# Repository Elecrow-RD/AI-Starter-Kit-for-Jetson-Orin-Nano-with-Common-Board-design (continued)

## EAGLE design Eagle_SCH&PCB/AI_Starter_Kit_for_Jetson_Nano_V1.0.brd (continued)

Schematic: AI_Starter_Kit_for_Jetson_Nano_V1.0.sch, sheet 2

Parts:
BUZ1: BUZZER_1295; BUZZER_0955_DIP
C15, C33, C52, C53, C66, C67, C68, C69, C70, C72, C73, C76, C226: 1uF; C0603
C16, C18, C19, C20, C21, C22, C23, C24, C25, C26, C27, C28, C29, C30, C31, C32, C34, C35, C36, C37, C40, C49, C50, C54, C55, C58, C64, C74, C88, C95, C100, C112, C138, C144, C145, C146, C148, C149, C177, C209, C220: 100nF; C0603
C38, C39: 1nF; C0603
C41, C221, C227, C228: 10nF; C0603
C42: 22uF; C0805
C44, C45, C56, C71, C75, C77, C78, C79, C135, C147, C166, C213, C214: 4.7uF; C0603
C51, C80, C81: 220nF; C0603
C86, C136, C139: 2.2uF; C0603
C101, C102: 33pF; C0603
C105, C106: 330pF; C0603
C107, C109, C111, C179: 15pF; C0603
C129, C222, C224: 22nF; C0603
C133, C134, C212: 12pF; C0603
C176, C178, C223: 10uF; C0805
C225: 47uF; C0805
D001, D003: 1N4148; D_SOD123
D11: RED; LED-8MM
EC1: Encoder; 5P-13.75X11.7X6.5H
FB6, FB10: 10uH; L0603
FB9: FB 220R/MH2012HM221-T; L0805
J1, J4: H_22_2.54; P4_2.54*4_VIA
J2: Gas Sensor Socket; MQ2
J3: ST150(ZD); 2*2P-IR928
J5, J6, J21, J22: PH2.0-4P; 4P-SMD-2.0
J9: SERVO_1; 1X03
J10: SERVO_2; 1X03
J12: IR-3PSIP3; VS1838B-SIP3
J14: RGB6464AMD; RGB64*64AMD
J23: SERVO; 4P-SMD-2.0
J123: 3.5MM3P; 3.5MM*3P
J138: CROWPI_POW_SMD-2.54MM5P; CROWPI_POW_SMD-5P*2.54
J233: Ultrasonic; ULTRA
J313: MOTOR_1CN; MOTOR_1CM
K1, K2, K3, K4: BUTTON_2P
K5: ROCKER
K6, K7: BUTTON; 157SW
K10: RELAY-SRD; REY5-6-19.1X15.5X15.3MM
K11: TILT-DIP-2P; TILT
L14: CD32_950MA; CD32
L103, L104: 2.2uH; 0805@1
LED1, LED6: RED; DISCRETE_LED-0603
P1, P2, P3, P4, P5, P6, P10, P13, P17, P25, P26, P27, P28, P29, P30, P31, P32, P33, P34, P35, P36, P37, P38, P39, P40, P41, P42, P43, P44, P45, P46, P47, P55, P56, P57, P59, P60, P61, P62, P63, P69, P70, P73, P74, P76, P77, P78, P79, P80, P81, P82, P83, P84, P109, P110, P111, P112, P113, P114, P115, P116: PADPAD-1.0MM; PAD-1.0MM
P66, P104: TEST_PAD; TEST_PAD-1.0MM
P75, P105, P106, P107, P108: IO_RGB; PAD-1.0MM
P101: KEY; 1P-D450
Q3, Q5, Q103, Q104, Q108, Q115: S9013; SOT23@1
Q6, Q9: AO3401A; PMOS_SOT23
Q7, Q8, Q106, Q107: BSS138; SOT23
R1, R100: 100K; R0603
R13: 5.1R; R0603
R14, R23, R29, R30, R31, R43, R45, R72, R73, R81, R84, R85, R101, R108, R131, R132, R133, R134, R239, R240, R248, R257, R259: 4.7K; R0603
R15: MF52A103F3950; RES-TH_L2.5-W2.5-P1.70-D0.3
R16, R17, R21, R26, R27, R28, R36, R42, R63, R64, R65, R77, R87, R89, R94, R104, R109, R113, R127, R231, R237, R242, R249, R251, R253, R255, R273, R280, R286, R288, R302, R308, R324, R325: 10K; R0603
R18, R19, R102, R105, R106, R111, R189, R238, R256, R258, R260: NC; R0603
R22: 270R; R0603
R24, R32, R33, R35, R107, R140, R246, R282, R287, R321, R364, R639: 1K; R0603
R25, R71: 470R; R0603
R34, R39, R82, R83, R128, R129, R135, R136, R221, R243, R272, R298: 0R; R0603
R74, R254, R299: 2K; R0603
R75, R76: 47K; R0603
R79, R110: 4.7k; R0603
R112, R284: 100R; R0603
R115, R116, R125, R130, R276, R283, R292, R293, R294, R297, R303: 22R; R0603
R219: 30.9K; R0603
R244: 130K; R0603
R245: 500K; 3P-SMD-SQUA-3.6X3.3
R247, R250, R252: 1M; R0603
R268: 10K; 3P-SMD-SQUA-3.6X3.3
R328: 5.1K; R0603
R367: 820R; R0603
R652: 2.7K; R0603
R653: 3.74K; R0603
R654: 5.6K; R0603
R655: 8.2K; R0603
RP1: R-POTENTIOMETER; 3P-SQUA-45.6X10X5.8H
SW1: switch_6pin; SWITCH_6PIN_2P
U2: LSM6DS3TR-C; LGA-14L
U4: KTH1701FH-ST3; SOT-23W
U6, U7: RT9013-33GB-MS; SOT23-5
U8, U35: MMDT3906; SOT-363
U9: DHT20; CROWTAIL-DHT20-V1.0-20211013_DHT20
U13: SPL06-001; LGA8-0.65-2X2.5X0.95MM
U16: TCA9534APWR; SOP65P640X120-16N
U18: KT0210-QFN40-EP; QFN40_EP
U19: WMM7027ATSN1-4/TR; LGA-4(1.9X2.8)
U24: SN74LVC1G125; SOT23-5
U25: MT2492; MT2492-SOT23-6
U27: RP2040_RP2040; RP2040_QFN-56
U29: SELF_W25Q128JV; SELF_SOIC-8-208MIL
U31: STC8H1K28-36I-LQFP32; QFP80P900X900X165-32N
U39: PCF8574DWR(UMW); SO-16-300MIL
U103: LPW5206AB5F; IC_SOT23-5
U114: ULN2003D
U115: MFRC522; RC522
U121: BH1750; B1750
U123: TTP223; SOT23-6L
U125: LM358; SOP8@1
U126: BISS0001DRG; SOP16
U131: D203S; PIR_MOTION_SENSOR_3P-D8.1MM
U205: HT16K33-20P; HT16K33-SOP20
U215: YY2841AS-33; 4-DIGITAL_DISPLAY
U235: LCD1602; LCD1206
U$66, U$69, U$70, U$71, U$164, U$165: PADPAD1; PAD_5*3
X2: 12MHZ_SMD3225; A_XBJ_SMD3225
X102: 27.12MHZ; CRYSTAL-3.2-2.5

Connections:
3V3_IO: J5.3, J6.3, J23.3, P41.P$1, P83.P$1, Q9.2 (S), U8.4 (E2)
5V_IO: J21.3, J22.3, P79.P$1, Q6.2 (S), U35.4 (E2)
5V_SERVO_1: J10.3, P35.P$1, Q8.3 (D), R134.2
5V_SERVO_2: J9.3, P33.P$1, Q7.3 (D), R133.2
+1V1: C23.1, C64.1, C86.1, U27.23 (VDD_1V1), U27.45 (LDO_OUT), U27.50 (VDD_1V1)
+5V_SYS: C16.2, C19.2, C30.2, C31.2, C32.1, C35.2, C40.1, C42.1, C45.1, C54.1, C56.1, C67.1, C69.1, C74.2, C176.1, FB9.2, J4.1, J4.1-1, J9.2, J10.2, J138.P$1 (1), P36.P$1, P42.P$1, Q6.3 (D), R17.1, R25.1, R29.1, R72.1, R73.1, R74.1, R87.1, R89.1, R127.1, R133.1, R134.1, R257.1, R259.1, R268.3 (2), R283.1, R303.1, R324.1, SW1.2 (2_COM2), U6.1, U6.3, U7.1, U7.3, U16.16 (VCC), U18.7 (VDD5V), U18.24 (VDD5V_DRI), U25.5 (IN), U35.1 (E1), U39.P$16 (VDD), U114.9 (COM), U205.P$20, U235.P$2 (2_VDD), U235.P$15 (15_LEDA); also elsewhere on the board
+5V_SYS_GAS: C25.2, J2.1 (A), J2.2 (H), J2.3 (A), R101.2, SW1.3 (3_2A)
A: U205.P$17, U215.11 (11_A)
ADC_CH0: K5.P$2 (COM1), P62.P$1, U31.1 (ADC0/P1.0)
ADC_CH1: K5.P$5 (COM2), P63.P$1, U31.2 (ADC1/P1.1)
ADC_CH2: C21.2, P113.P$1, RP1.2 (3), U31.3 (ADC2/P1.2)
ADC_CH3: J2.4 (B), J2.6 (B), P116.P$1, R14.1, U31.4 (ADC3/P1.3)
ADC_CH4: P61.P$1, R639.2, R652.2, R653.2, R654.2, R655.2, U31.5 (ADC4/P1.4)
ADC_CH5: C26.2, P70.P$1, R15.1, R16.2, U31.6 (ADC5/P1.5)
ANT1: R128.2, R129.2
AVDD: C136.1, R34.1, U27.43 (ADC_VDD)
AVDD3V: C53.1, C76.2, U18.6 (VDD2P8V), U18.27 (VDD2P8V_CG)
B: U205.P$16, U215.7 (7_B)
BOOT: K6.2, P10.P$1, P69.P$1, R35.2
BUZZER: P114.P$1, R284.1, U31.31 (ADC10/P0.2)
C: U205.P$15, U215.4 (4_C)
COM: J123.2, K10.2
CSB: U13.2 (CSB)
D: U205.P$14, U215.2 (2_D)
D2/I2C1_SDA: Q107.2 (S), R18.1, R39.2, R240.2, R260.1, U2.14 (SDA), U9.2 (SDA), U13.3 (SDA), U31.25 (I2CSDA_2/P2.4), U121.4 (SDA); also elsewhere on the board
D3/I2C1_SCL: Q106.2 (S), R19.1, R239.2, R258.1, R272.2, U2.13 (SCL), U9.4 (SCL), U13.4 (SCL), U31.26 (I2CSCL_2/P2.5), U121.6 (SCL); also elsewhere on the board
D4: P84.P$1, R298.2, R364.2; also elsewhere on the board
D6: C33.1, P13.P$1, R63.1, U4.2 (VOUT); also elsewhere on the board
D8/SPI0_CS0: U115.24 (SDA/NSS/RX); also elsewhere on the board
D9/SPI0_MISO: U115.31 (D7/MISO/SCL/TX); also elsewhere on the board
D10/SPI0_MOSI: U115.30 (D6/ADR_0/MOSI); also elsewhere on the board
D11/SPI0_SCK: U115.29 (D5/ADR_1/SCK/DTRQ); also elsewhere on the board
D12/PWM: J6.1, P81.P$1; also elsewhere on the board
D13/PWM: J5.1, P82.P$1; also elsewhere on the board
D14/UART1_TXD: R125.1; also elsewhere on the board
D15/UART1_RXD: R130.1; also elsewhere on the board
D16/UART1_CTS: J233.P$3 (3_TRIG), P111.P$1; also elsewhere on the board
D17/UART1_RTS: P55.P$1, R287.2; also elsewhere on the board
D18/I2S0_SCLK: P27.P$1, R24.2; also elsewhere on the board
D20/I2S0_SDIN: J12.3, P112.P$1, R140.1; also elsewhere on the board
D23/SPI1_CS1: P57.P$1, R189.1, R254.2; also elsewhere on the board
D25/SPI1_MISO: P109.P$1, U125.1 (1_OUT1), U125.2 (2_IN1-); also elsewhere on the board
D26/SPI1_MOSI: P110.P$1, R299.2; also elsewhere on the board
D27/SPI1_SCK: P2.P$1, R282.1; also elsewhere on the board
DB4: U39.P$9 (P4), U235.P$11 (11_D4)
DB5: U39.P$10 (P5), U235.P$12 (12_D5)
DB6: U39.P$11 (P6), U235.P$13 (13_D6)
DB7: U39.P$12 (P7), U235.P$14 (14_D7)
DIG1: U205.P$2, U215.12 (12_COM1)
DIG2: U205.P$3, U215.9 (9_COM2)
DIG3: U205.P$4, U215.8 (8_COM3)
DIG4: U205.P$5, U215.6 (6_COM4)
DIS_RGB: P74.P$1, U27.41 (GPIO29/ADC3)
DP: U205.P$10, U215.3 (3_DP)
E: U205.P$13, U215.1 (1_E)
ENCODER_A: C38.1, P59.P$1, R64.1, U16.11 (P6)
ENCODER_B: C39.2, P60.P$1, R65.1, U16.12 (P7)
ENCODER_SW: C66.2, R71.1, R74.2, U16.10 (P5)
E_LCD: U39.P$6 (P2), U235.P$6 (6_E)
F: U205.P$12, U215.10 (10_F)
G: U205.P$11, U215.5 (5_G)
GND: C15.1, C16.1, C18.1, C19.1, C20.2, C21.1, C22.2, C23.2, C24.2, C25.1, C26.1, C27.1, C28.1, C29.1, C30.1, C31.1, C32.2, C33.2, C34.1, C35.1, C36.1, C37.2, C38.2, C39.1, C40.2, C41.1, C42.2, C44.2, C45.2, C49.1, C53.2, C54.2, C55.1, C56.2, C58.1, C64.2, C66.1, C67.2, C68.2, C69.2, C70.2, C71.2, C72.2, C73.1, C74.1, C75.1, C76.1, C77.1, C78.1, C86.2, C88.2, C95.2, C101.2, C102.1, C105.1, C106.2, C111.1, C112.1, C133.2, C134.1, C135.2, C136.2, C138.2, C139.2, C144.2, C145.2, C146.2, C147.2, C148.2, C149.2, C166.2, C176.2, C177.1, C178.1, C179.1, C209.1, C212.1, C213.1, C214.1, C220.1, C221.1, C225.1, C226.2, C227.2, C228.2, EC1.2 (C), EC1.4 (GND), J1.3, J1.3-1, J3.1 (-), J3.3 (E), J4.3, J4.3-1, J5.4, J5.SS1, J5.SS2, J6.4, J6.SS1, J6.SS2, J9.1, J10.1, J12.2, J14.2, J14.4, J14.5, J14.6, J21.4, J21.SS1, J21.SS2, J22.4, J22.SS1, J22.SS2, J23.4, J23.SS1, J23.SS2, J138.P$6 (6), J138.P$7 (7), J233.P$1 (1_GND), K1.P$1, K2.P$1, K3.P$1, K4.P$1, K6.1, K7.1, K11.1, LED6.-, P17.P$1, P32.P$1, P37.P$1, P38.P$1, P43.P$1, P73.P$1, P80.P$1, Q3.2 (E), Q5.2 (E), Q103.2 (E), Q104.2 (E), Q108.2 (E), Q115.2 (E), R1.2, R13.1, R14.2, R15.2, R21.1, R23.2, R30.1, R31.1, R42.1, R75.2, R76.2, R77.2, R82.1, R83.1, R94.2, R100.2, R105.2, R108.1, R109.1, R111.1, R189.2, R238.1, R242.1, R250.2, R256.1, R268.1, R273.1, R280.1, R286.2, R288.2, R302.1, RP1.1, U2.6 (GND), U2.7 (GND), U4.3 (GND), U6.2, U7.2, U9.3 (GND), U13.1 (GND), U13.7 (GND), U16.1 (A0), U16.2 (A1), U16.8 (GND), U18.16 (DVSS), U18.34 (AUGND), U18.39 (DRVSS), U18.41 (GND), U19.2 (GND), U19.3 (GND), U24.1 (OE), U24.3 (GND), U25.2 (GND), U27.19 (TESTEN), U27.EPAD (GND), U29.4 (GND), U31.12 (GND/AGND), U39.P$8 (VSS), U103.2 (2_GND), U114.8 (GND), U115.1 (I2C), U115.4 (DVSS), U115.5 (PVSS), U115.10 (TVSS), U115.14 (TVSS2), U115.18 (AVSS), U115.33 (GND), U121.3 (GND\), U123.2 (GND), U125.4 (4_GND), U126.7 (VSS), U131.3 (G), U205.P$1, U235.P$1 (1_VSS), X2.2 (GND), X2.4 (GND), X102.2 (GND), X102.4 (GND); also elsewhere on the board
IN1: C212.2, P101.1, U123.3 (IN)
IN1+: R28.2, U125.3 (3_IN1+), U125.7 (7_OUT2)
INT1: P66.P$1, U2.4 (INT1)
INT2: P104.P$1, U2.9 (INT2)
IO_RGB: P75.P$1, U27.29 (GPIO18)
IO_RGB_POWER_EN: P76.P$1, U27.40 (GPIO28/ADC2)
ITR9606_IN: C41.2, J3.4 (C), P25.P$1, R27.2, U125.6 (6_IN2-)
JS_3V3: C15.2, C18.2, C24.1, C27.2, C28.2, C34.2, C37.1, C58.2, C70.1, C177.2, C178.2, C213.2, C214.2, C220.2, C226.1, J1.1, J1.1-1, J12.1, J233.P$4 (4VCC), Q7.1 (G), Q8.1 (G), Q9.3 (D), Q106.1 (G), Q107.1 (G), R16.1, R18.2, R19.2, R22.2, R26.1, R27.1, R28.1, R43.2, R45.1, R63.2, R84.1, R85.1, R113.2, R131.2, R132.2, R140.2, R237.2, R239.1, R240.1, R249.2, R251.2, R255.2, R308.1, R325.1, R364.1, R639.1, RP1.3 (2), U2.5 (VDDIO), U2.8 (VDD), U4.1 (VCC), U8.1 (E1), U9.1 (VCC), U13.6 (VDDIO), U13.8 (VDD), U31.10 (VCC/AVCC), U31.11 (ADC_VREF+), U115.2 (PVDD), U115.3 (DVDD), U115.12 (TVDD), U115.15 (AVDD), U121.1 (VCC), U123.5 (VCC), U125.8 (8_VCC), U126.11 (VDD), U131.1 (D); also elsewhere on the board
LIGHT: R321.2, U39.P$7 (P3)
MIC_3V3: C49.2, U7.5, U19.4 (VDD)
MIC_BIAS: C51.1, R79.1, R110.1, U18.3 (MIC_BIAS)
MIC_IN: C50.2, R110.2, U18.2 (KEY_IN)
MIC_USB_D+: R116.1; also elsewhere on the board
MIC_USB_D-: R115.1; also elsewhere on the board
unnamed: LED1.+, R81.1
unnamed: R1.1, U35.2 (B1), U35.5 (B2), U35.6 (C1)
unnamed: R17.2, U39.P$1 (A0)
unnamed: R87.2, U39.P$2 (A1)
unnamed: R89.2, U39.P$3 (A2)
unnamed: P6.P$1, U31.21 (P2.0)
unnamed: P5.P$1, U31.22 (P2.1)
unnamed: P4.P$1, U31.23 (P2.2)
unnamed: P3.P$1, U31.24 (P2.3)
unnamed: J1.2, J1.2-1, R135.1
unnamed: J1.4, J1.4-1, R136.1
unnamed: R42.2, R268.2 (3), U235.P$3 (3_V0)
unnamed: Q5.3 (C), U235.P$16 (16_LED_K)
unnamed: Q108.1 (B), R77.1, R321.1
unnamed: R82.2, U2.2 (SDX)
unnamed: J2.5 (H), R13.2
unnamed: C133.1, U27.20 (XIN), X2.1 (XIN)
unnamed: Q3.1 (B), R21.2, R24.1
unnamed: EC1.5 (SW), R71.2
unnamed: R244.1, R245.1
unnamed: R251.1, U126.8 (!RESET)
unnamed: J3.2 (+), R22.1
unnamed: R105.1, U103.3 (3_SET)
unnamed: R26.2, R94.1, U125.5 (5_IN2+)
unnamed: R221.2, U24.2 (IN_A)
unnamed: R29.2, U16.13 (INT)
unnamed: C209.2, R113.1, U121.5 (DVI)
unnamed: R127.2, U16.3 (A2)
unnamed: K5.P$1, R23.1
unnamed: C100.1, R328.1
unnamed: K5.P$6, R30.2
unnamed: K5.P$3, R43.1
unnamed: K5.P$4, R45.2
unnamed: R33.2, U27.21 (XOUT)
unnamed: P105.P$1, U27.2 (GPIO0)
unnamed: J313.P$2, Q104.3 (C)
unnamed: P106.P$1, U27.3 (GPIO1)
unnamed: P107.P$1, U27.4 (GPIO2)
unnamed: Q6.1 (G), R75.1, U35.3 (C2)
unnamed: R100.1, U8.2 (B1), U8.5 (B2), U8.6 (C1)
unnamed: R83.2, U2.3 (SCX)
unnamed: R84.2, U2.12 (CS)
unnamed: P108.P$1, U27.5 (GPIO3)
unnamed: D11.2 (C), Q3.3 (C)
unnamed: Q9.1 (G), R76.1, U8.3 (C2)
unnamed: K11.2, R298.1
unnamed: C129.1, L14.1, U25.6 (SW)
unnamed: LED6.+, R101.1
unnamed: D11.1 (A), R25.2
unnamed: R85.2, U2.1 (SDO)
unnamed: C50.1, R79.2, R102.1, U19.1 (OUT)
unnamed: C51.2, C52.2, U18.4 (DRVSS_SNS)
unnamed: R31.2, U13.5 (SDO)
unnamed: R108.2, R219.1, U25.3 (BF)
unnamed: Q108.3 (C), R32.2, R324.2
unnamed: C129.2, U25.1 (BS)
unnamed: R107.2, R109.2, U25.4 (EN)
unnamed: Q5.1 (B), R32.1
unnamed: C52.1, U18.5 (VREF_1P8V)
unnamed: FB10.2, U18.8 (DCDC1_SW)
unnamed: C71.1, FB10.1, U18.9 (DVDD1V)
unnamed: C72.1, U18.10 (DVDD3V)
unnamed: R111.2, U18.13 (GPIO6)
unnamed: R115.2, U18.22 (DM)
unnamed: R116.2, U18.21 (DP)
unnamed: C73.2, U18.23 (VDD3V_USB)
unnamed: FB6.1, U18.25 (DCDC2_SW)
unnamed: C75.2, FB6.2, U18.26 (VDD1P8V_CP)
unnamed: R104.1, U103.4 (4_EN)
unnamed: C77.2, U18.29 (CHP)
unnamed: C78.2, U18.28 (CHN)
unnamed: C79.1, U18.31 (CFLYP)
unnamed: C79.2, U18.30 (CFLYN)
unnamed: C134.2, R33.1, X2.3 (XOUT)
unnamed: C80.1, U18.35 (VINP)
unnamed: C81.1, U18.36 (VINN)
unnamed: P28.P$1, U18.12 (GPIO4)
unnamed: P29.P$1, U18.11 (GPIO3)
unnamed: K1.P$2, R652.1
unnamed: K2.P$2, R653.1
unnamed: K3.P$2, R654.1
unnamed: K4.P$2, R655.1
unnamed: R39.1, U27.31 (GPIO20)
unnamed: R272.1, U27.32 (GPIO21)
unnamed: R237.1, R238.2, U121.2 (ADDR)
unnamed: Q115.1 (B), R112.2, R273.2
unnamed: C29.2, J313.P$1, R283.2
unnamed: R288.1, U123.4 (AHLB), U123.6 (TOG)
unnamed: Q104.1 (B), R280.2, R282.2
unnamed: R286.1, R287.1, U123.1 (OUT)
unnamed: J138.P$2 (2), R297.2
unnamed: J138.P$3 (3), R292.2
unnamed: J138.P$4 (4), R293.2
unnamed: J138.P$5 (5), R294.2
unnamed: J233.P$2 (2_ECHO), R299.1
unnamed: Q103.1 (B), R284.2, R302.2
unnamed: BUZ1.2 (2-), D001.+, Q103.3 (C)
unnamed: BUZ1.1 (1+), C55.2, D001.-, R303.2
unnamed: R253.1, U126.3 (RR1)
unnamed: C228.1, R253.2, U126.4 (RC1)
unnamed: R254.1, U126.2 (VO)
unnamed: R252.1, U126.6 (RR2)
unnamed: C227.1, R252.2, U126.5 (RC2)
unnamed: C222.1, R245.2 (3), R245.3 (2), U126.12 (2OUT)
unnamed: C222.2, R244.2, R246.2, U126.13 (2IN-)
unnamed: R249.1, U126.9 (VC)
unnamed: R250.1, U126.10 (IB)
unnamed: C221.2, R242.2, R243.1, U131.2 (S)
unnamed: C223.2, C224.1, R247.1, U126.16 (1OUT)
unnamed: C224.2, R247.2, R248.2, U126.15 (1IN-)
unnamed: C223.1, R246.1
unnamed: C225.2, R248.1
unnamed: R255.1, R256.2, U126.1 (A)
unnamed: R243.2, U126.14 (1IN+)
unnamed: C111.2, U115.22 (OSCOUT), X102.1 (C1)
unnamed: C179.2, U115.21 (OSCIN), X102.3 (C2)
unnamed: C112.2, R367.1, U115.16 (VMID)
unnamed: C100.2, R367.2, U115.17 (RX)
unnamed: L104.1, U115.13 (TX2)
unnamed: L103.1, U115.11 (TX1)
unnamed: C101.1, C109.2, L103.2, R328.2
unnamed: C102.2, C107.2, L104.2
unnamed: R325.2, U115.6 (NRSTPD)
unnamed: R308.2, U115.32 (EA)
unnamed: C105.2, C109.1, R128.1
unnamed: C106.1, C107.1, R129.1
NC: J123.1, K10.4
NO: J123.3, K10.5
OUT1_S: P47.P$1, R297.1, U114.16 (OUT1)
OUT2_S: P46.P$1, R292.1, U114.15 (OUT2)
OUT3_S: P45.P$1, R293.1, U114.14 (OUT3)
OUT4_S: P44.P$1, R294.1, U114.13 (OUT4)
QSPI_CS: R35.1, R36.1, U27.56 (QSPI_!CS!), U29.1 (/CS)
QSPI_D0: U27.53 (QSPI_SD0), U29.5 (DI(IO0))
QSPI_D1: U27.55 (QSPI_SD1), U29.2 (DO(IO1))
QSPI_D2: U27.54 (QSPI_SD2), U29.3 (/WP(IO2))
QSPI_D3: U27.51 (QSPI_SD3), U29.7 (/HOLD/RESET(IO3))
QSPI_SCK: U27.52 (QSPI_SCLK), U29.6 (CLK)
RELAY: P115.P$1, R112.1, U31.30 (ADC9/P0.1)
RESET: C20.1, K7.2, P26.P$1, R231.1, U27.26 (RUN)
RGB_CTRO: J14.3, P56.P$1, U24.4 (Y)
RING2: C80.2, U18.37 (RING2_REF), U18.38 (RING2)
RP2040_3V3: C22.1, C68.1, C88.1, C138.1, C139.1, C144.1, C145.1, C146.1, C148.1, C149.1, R34.2, R36.2, R231.2, U6.5, U27.1 (VDDIO), U27.10 (VDDIO), U27.22 (VDDIO), U27.33 (VDDIO), U27.42 (VDDIO), U27.44 (LDO_IN), U27.48 (USB_VDD), U27.49 (VDDIO), U29.8 (VCC)
RP2040_IO6_RGB: P34.P$1, R221.1, U27.8 (GPIO6)
RP2040_IO13_SERVO_1: Q8.2 (S), R132.1, U27.16 (GPIO13)
RP2040_IO14_SERVO_2: Q7.2 (S), R131.1, U27.17 (GPIO14)
RP2040_IO27_RGB_POWER_EN: P31.P$1, R107.1, U27.39 (GPIO27/ADC1)
RS: U39.P$4 (P0), U235.P$4 (4_RS)
RW: U39.P$5 (P1), U235.P$5 (5_RW)
RX: J23.2, P40.P$1, R130.2
SA: EC1.1 (A), R64.2, R72.2
SB: EC1.3 (B), R65.2, R73.2
SCL: J21.1, J22.1, P78.P$1, Q106.3 (D), R257.2, R258.2, U16.14 (SCL), U39.P$14 (SCL), U205.P$18
SDA: J21.2, J22.2, P77.P$1, Q107.3 (D), R259.2, R260.2, U16.15 (SDA), U39.P$15 (SDA), U205.P$19
SLEEVE: C81.2, R102.2, U18.1 (SLE_REF), U18.40 (SLEEVE)
STC8_RXD: R135.2, U31.13 (P3.0/RXD)
STC8_TXD: R136.2, U31.14 (P3.1/TXD)
STEP1: U16.4 (P0), U114.1 (IN1)
STEP2: U16.5 (P1), U114.2 (IN2)
STEP3: U16.6 (P2), U114.3 (IN3)
STEP4: U16.7 (P3), U114.4 (IN4)
TX: J23.1, P39.P$1, R125.2
USB_D+: J4.4, J4.4-1, U27.47 (USB_D+)
USB_D-: J4.2, J4.2-1, U27.46 (USB_D-)
V+: K10.1, R276.2
V-: D003.+, K10.3, LED1.-, Q115.3 (C)
VCC_DIS_RGB: C135.1, C147.1, L14.2, P1.P$1, R104.2, R106.1, R219.2, U103.5 (5_VIN)
VCC_RELAY: C36.2, D003.-, FB9.1, R81.2, R276.1
VCC_RGB: C44.1, C95.1, C166.1, J14.1, P30.P$1, R106.2, U24.5 (VCC), U103.1 (1_OUT)

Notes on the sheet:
I2C
Temperature & Humidity(DHT20)
3V-5.5V
ADD:0X38
ADDRESS:0X38
ADDRESS:0111000
LIGHT SENSOR
ADD:0X5C
2.7V-4.2V
ADDRESS:0x5C
ADDRESS:1011100
Accelerometer&Gyro
Digital display
ADDRESS:0X70
ADDRESS:1110000
I2C_LCD
Custom_key
Joystick
Linear Potentiometer
NFC
GAS-MQ2
NTC
Barometer
ADDRESS:0X76
Ultrasonic Sensor
Buzzer
I2C-EXIO-STC8-P0.2
Relay
IR Remote Sensor
Vibration sensor
TTP223
Touch Sensor
D17
Tilt sensor
gold
sliver
Encoder
PIR-Motion sensor
D23
8*8RGB_LED

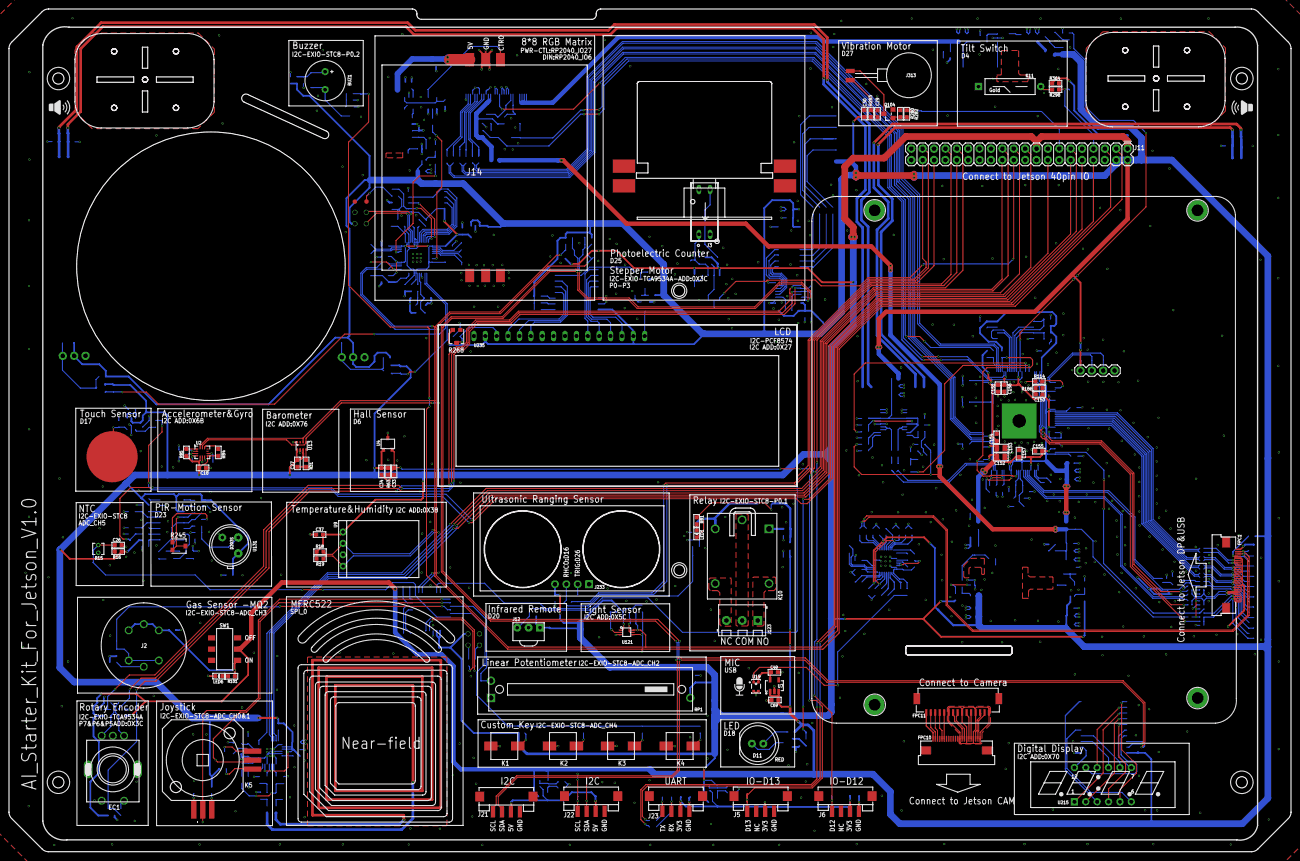
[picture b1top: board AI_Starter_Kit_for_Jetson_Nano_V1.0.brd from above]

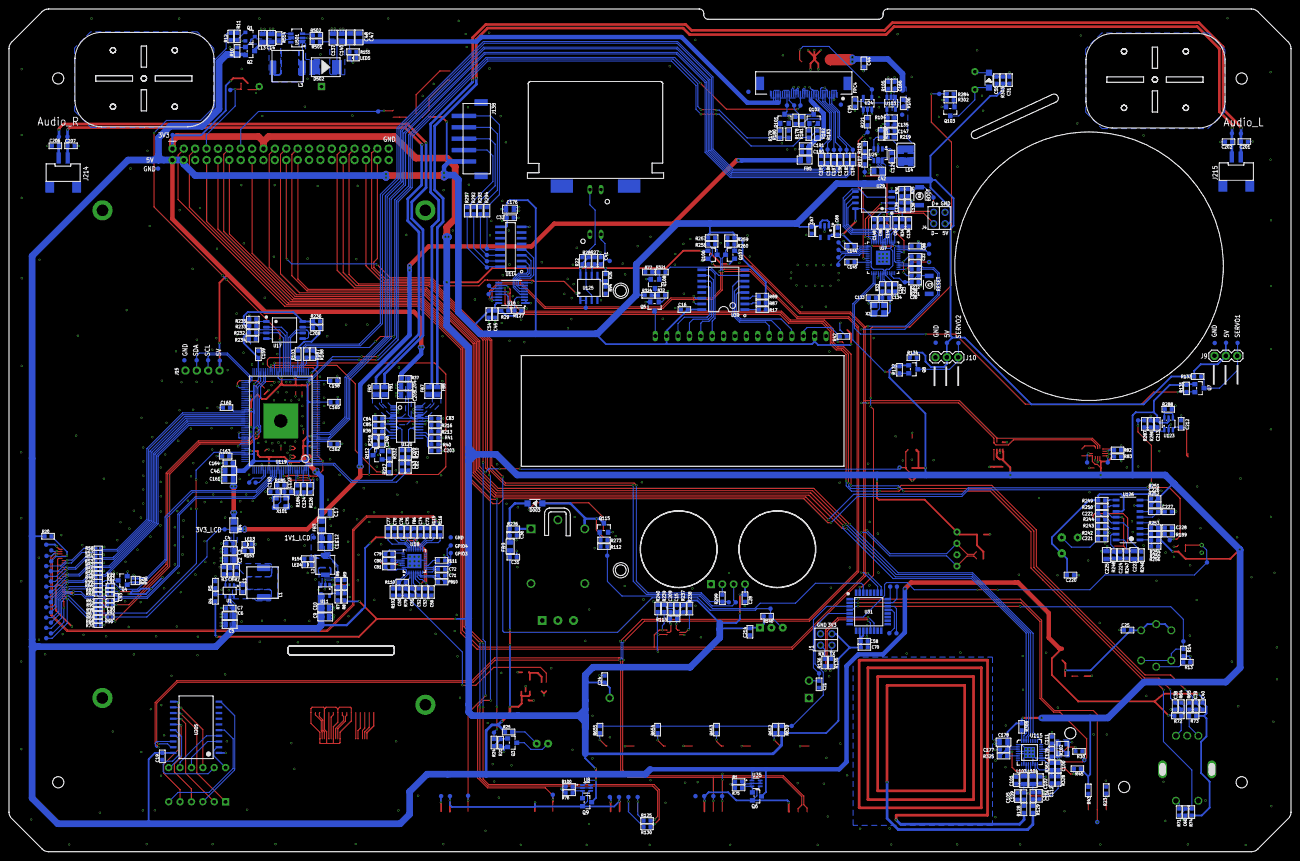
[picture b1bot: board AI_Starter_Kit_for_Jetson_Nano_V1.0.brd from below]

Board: 2 copper layers, 286.0 x 188.0 mm, 611 parts (521 on the bottom side), 374 nets.

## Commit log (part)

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2025-12-26 Add link to Ubuntu setup instructions in readme
    Updated instructions to include a link for setting up the Ubuntu environment.
2025-12-28 Update link reference for jetson file
2026-05-21 Update SD card image file to jetson20260519.img
    Updated the image file reference for flashing instructions.

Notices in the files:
parts and their libraries:
SparkFun-Connectors: Licensing: Creative Commons ShareAlike 4.0 International - https://creativecommons.org/licenses/by-sa/4.0
